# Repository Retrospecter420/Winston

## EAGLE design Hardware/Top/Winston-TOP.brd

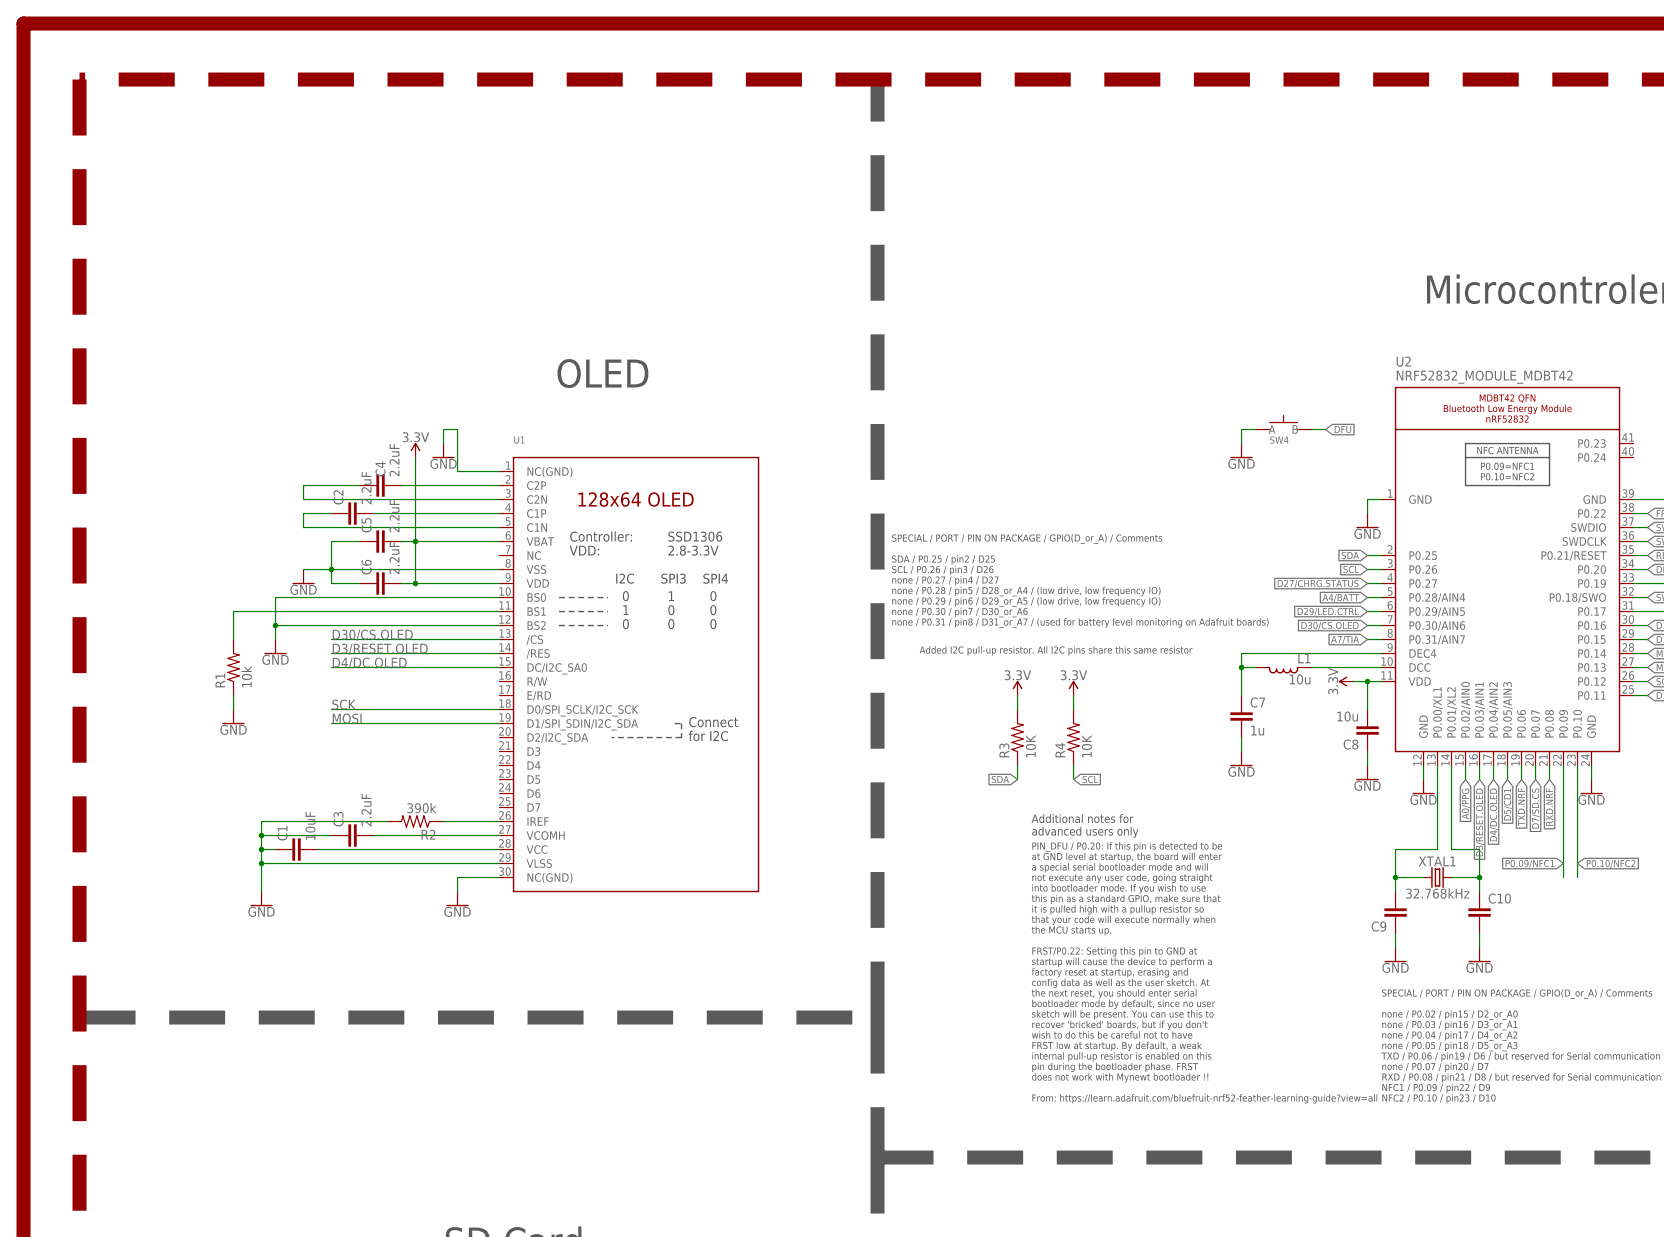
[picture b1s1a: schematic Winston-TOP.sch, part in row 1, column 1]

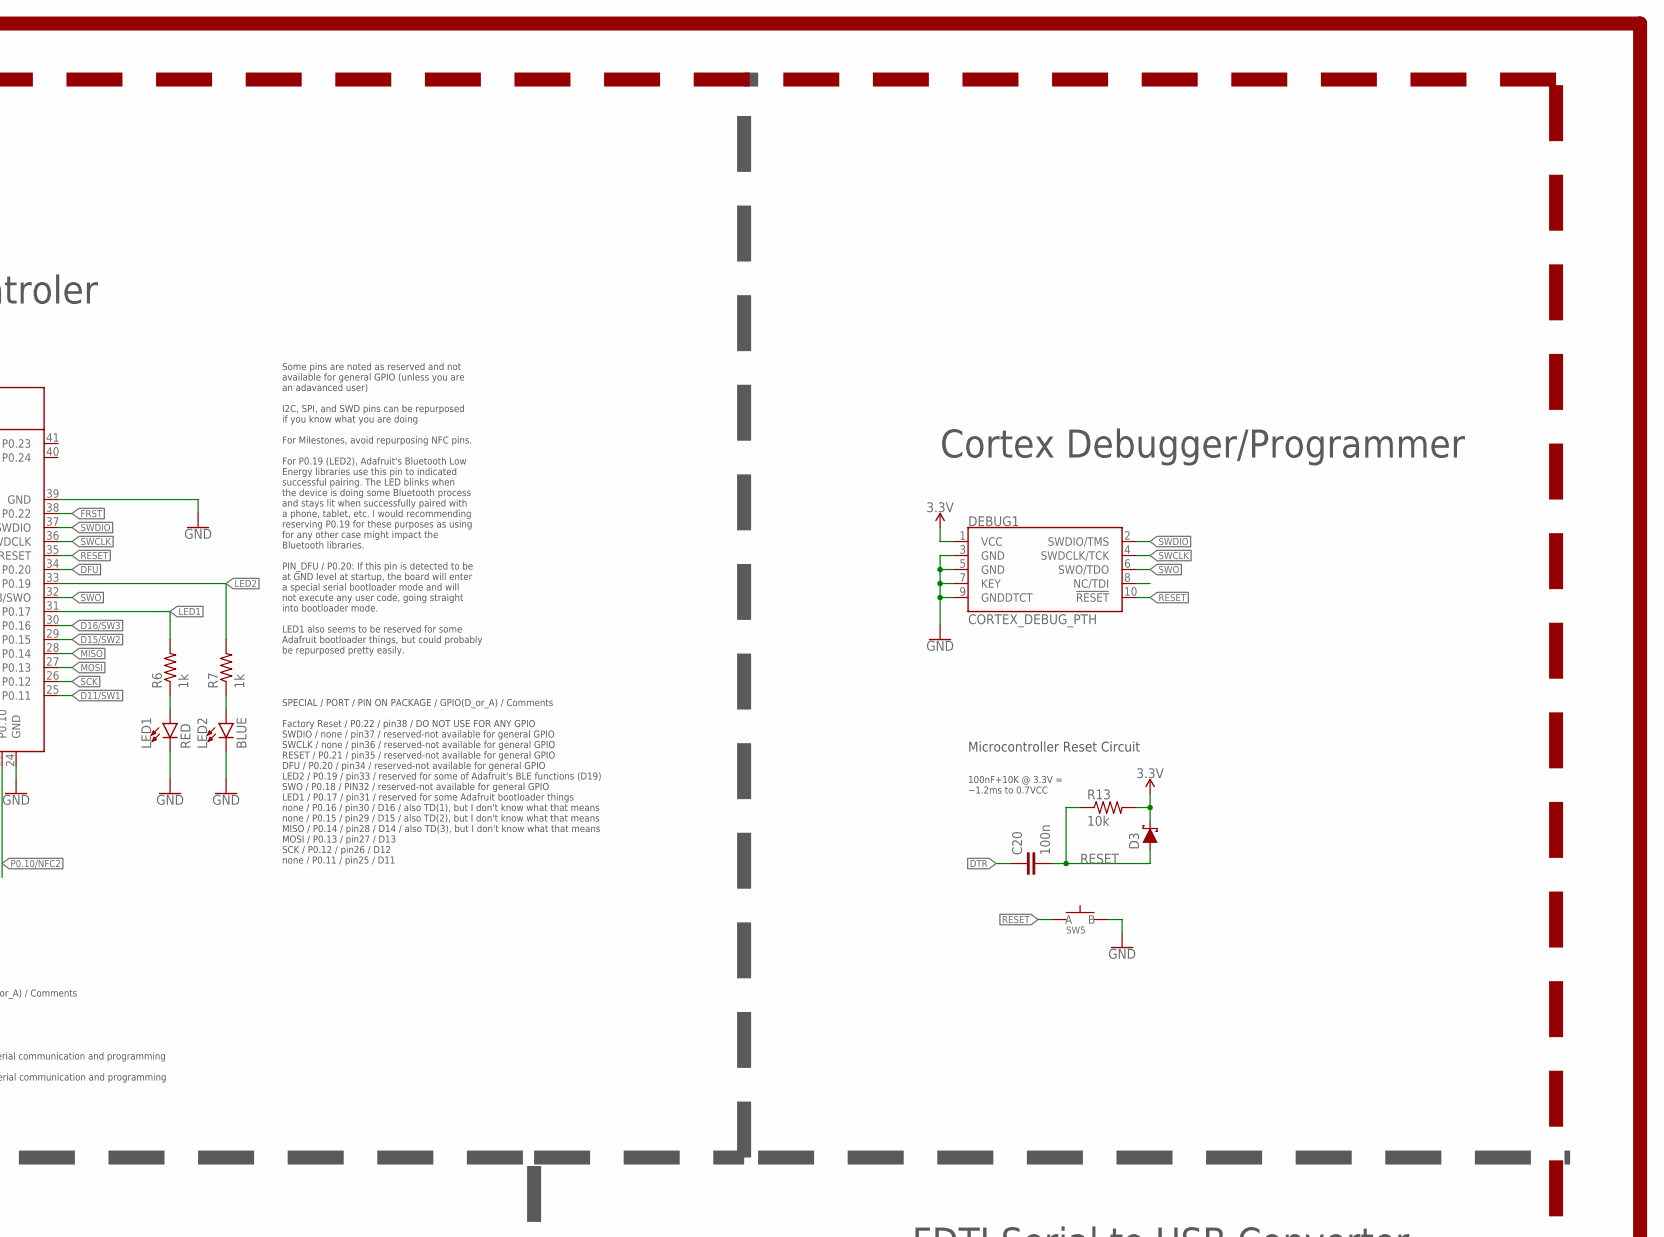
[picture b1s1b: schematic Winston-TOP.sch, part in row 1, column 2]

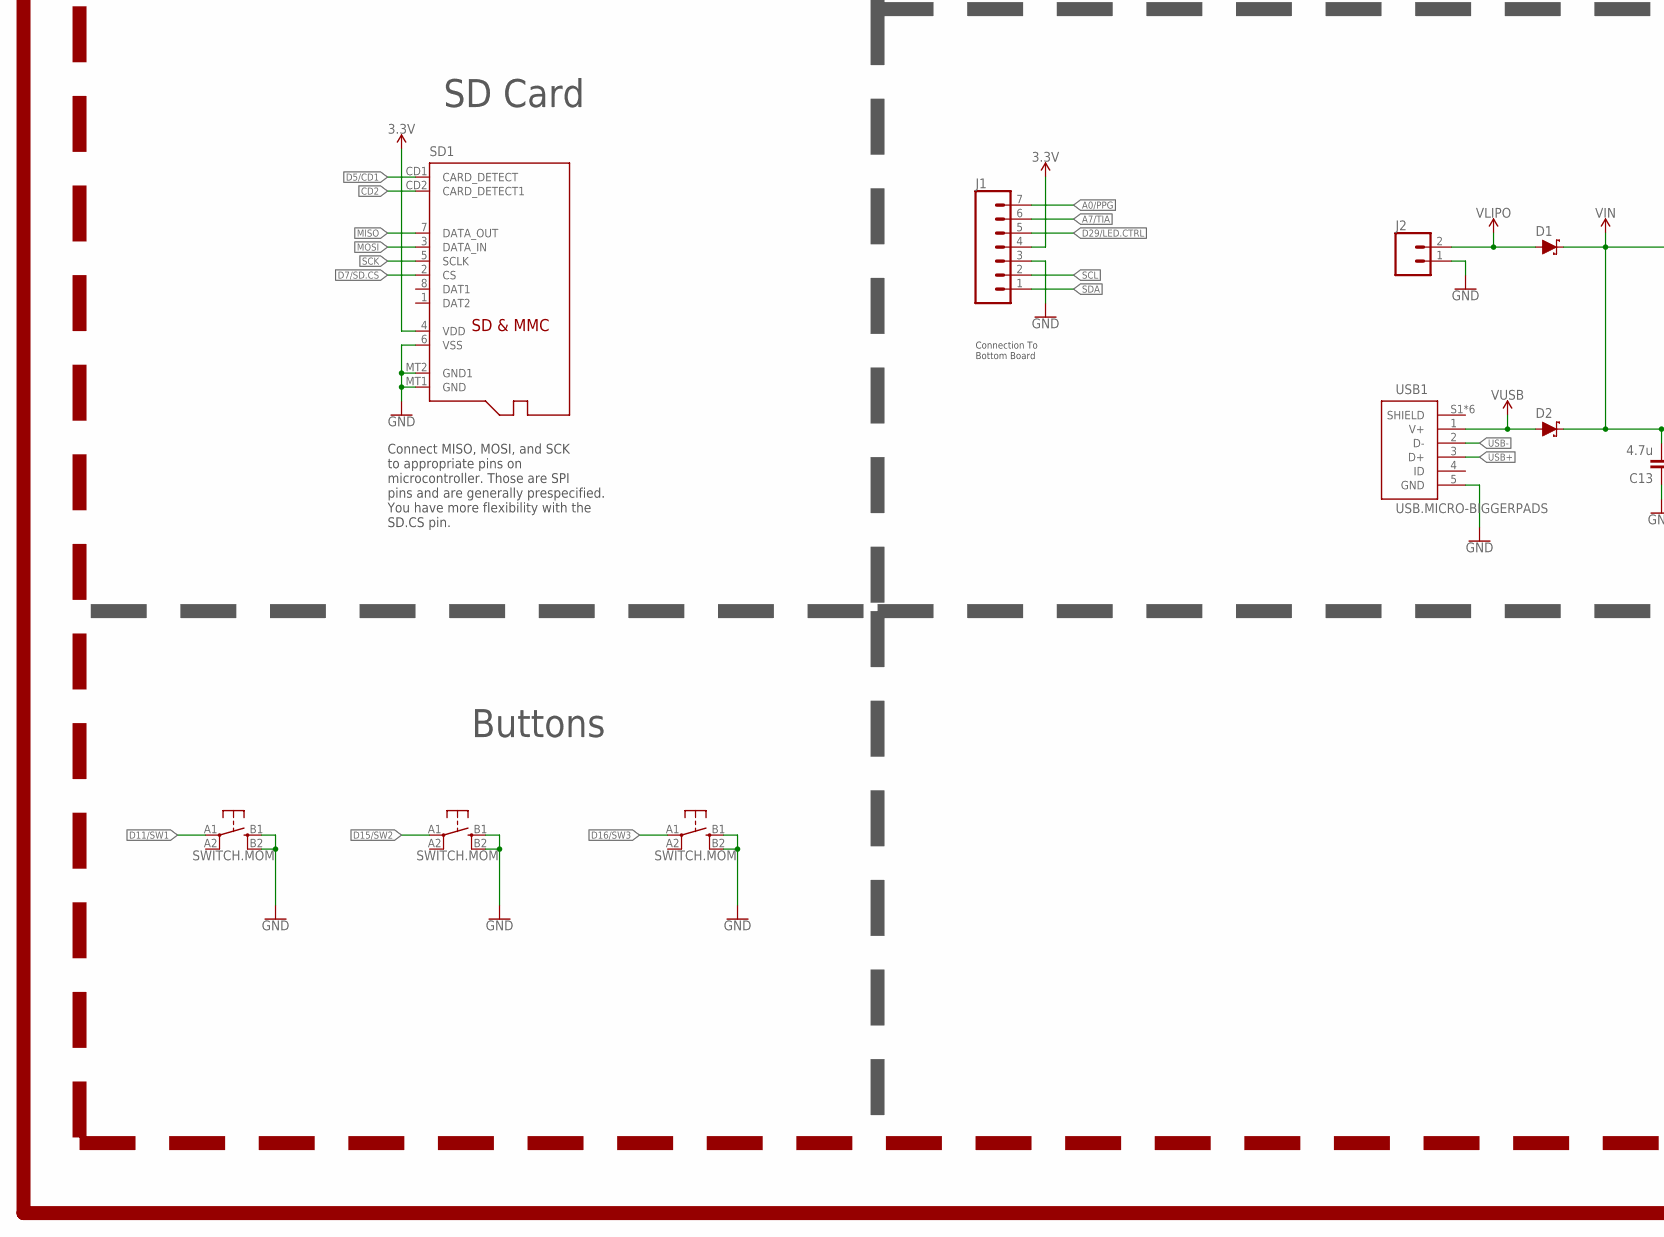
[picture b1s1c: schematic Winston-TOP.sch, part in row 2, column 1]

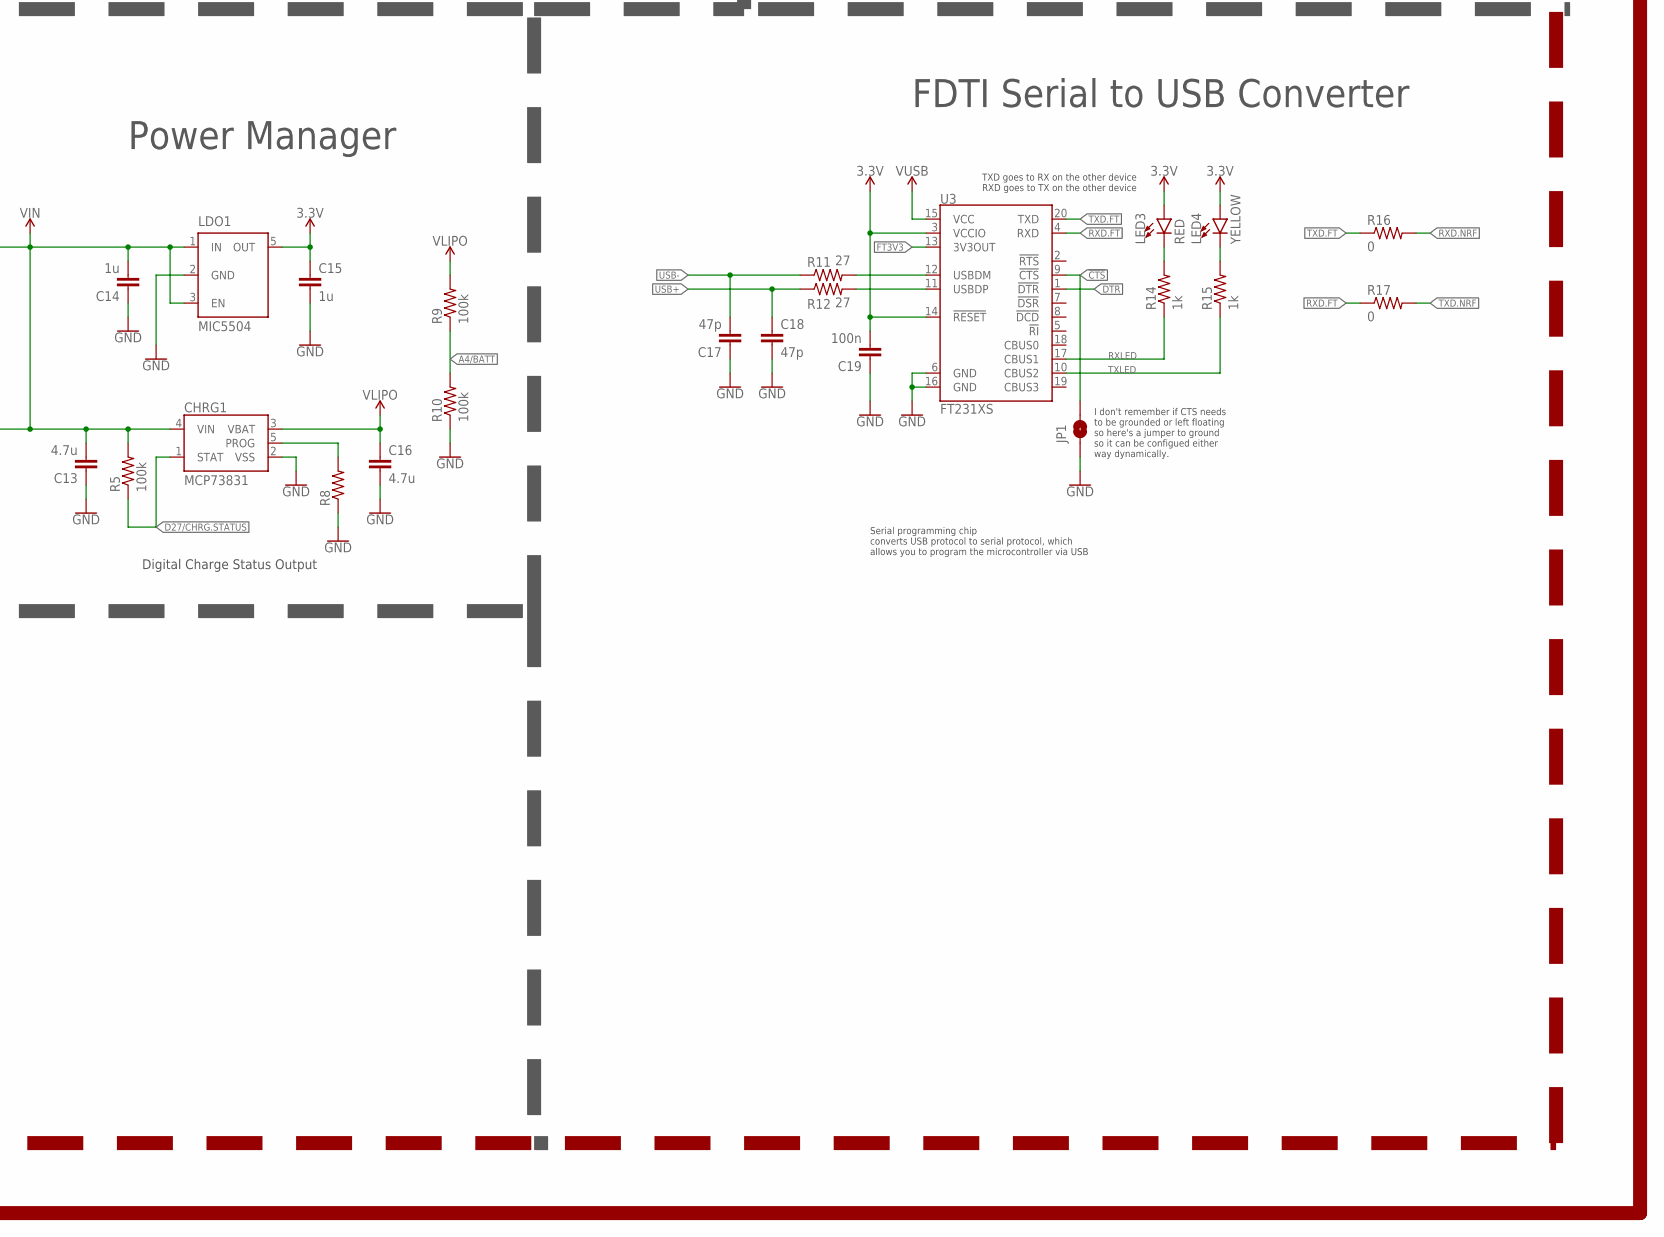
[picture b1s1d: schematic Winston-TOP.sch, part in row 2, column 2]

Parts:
C1: 10uF; C0603
C2, C3, C4, C5, C6: 2.2uF; C0402
C7, C14, C15: 1u; C0603
C8: 10u; C0805
C9, C10: CAPACITOR0603; C0603
C13, C16: 4.7u; C0603
C17, C18: 47p; C0603
C19, C20: 100n; C0603
CHRG1: MCP73831; SOT23-5
D1, D2, D3: SCHOTTKY-USC; USC
DEBUG1: CORTEX_DEBUG_PTH; 2X5-PTH-1.27MM
J1: CONN_07-1.27MM; 1X07_1.27MM
J2: CONN_02; 1X02
JP1: JUMPER-SMT_2_NO_SILK; SMT-JUMPER_2_NO_SILK
L1: 10u; L0603
LDO1: MIC5504; SOT23-5
LED1, LED3: RED; LED-0603
LED2: BLUE; LED-0603
LED4: YELLOW; LED-0603
R1, R13: 10k; R0603
R2: 390k; R0603
R3, R4: 10K; R0603
R5, R9, R10: 100k; R0603
R6, R7, R14, R15: 1k; R0603
R8: RESISTOR0603; R0603
R11, R12: 27; R0603
R16, R17: 0; R0603
SD1: MICROSD
SW1, SW2, SW3: SWITCH.MOM; TACTILE_SWITCH_SMD_6.2MM_TALL
SW4, SW5: SPST-PTS830GG140-COPY.1-3; BUTTON-GULLWING
U1: DISP_OLED_UG-2864HSWEG01-NO-WRAPAROUND; UG-2864HSWEG01_0.96IN_NO-WRAPAROUND
U2: NRF52832_MODULE_MDBT42; BLE_MODULE_RAYTAC_MDBT42
U3: FT231XS; SSOP20_L
USB1: USB.MICRO-BIGGERPADS; USB-MICRO-01.BIGGERPADS
XTAL1: 32.768kHz; 2-SMD.NOLEAD.2.0MMTO1.2MM

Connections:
3.3V: C5.2, C6.2, C8.2, C15.1, C19.2, D3.- (C), DEBUG1.1 (VCC), J1.4, LDO1.5 (OUT), LED3.A, LED4.A, R3.2, R4.2, R13.2, SD1.4 (VDD), U1.6 (VBAT), U1.9 (VDD), U2.11 (VDD), U3.3 (VCCIO), U3.14 (!RESET)
!CTS: JP1.2, U3.9 (!CTS)
A0/PPG: J1.7, U2.15 (P0.02/AIN0)
A4/BATT: R9.1, R10.2, U2.5 (P0.28/AIN4)
A7/TIA: J1.6, U2.8 (P0.31/AIN7)
CD2: SD1.CD2 (CARD_DETECT1)
D3/RESET.OLED: U1.14 (/RES), U2.16 (P0.03/AIN1)
D4/DC.OLED: U1.15 (DC/I2C_SA0), U2.17 (P0.04/AIN2)
D5/CD1: SD1.CD1 (CARD_DETECT), U2.18 (P0.05/AIN3)
D7/SD.CS: SD1.2 (CS), U2.20 (P0.07)
D11/SW1: SW1.A1 (1), U2.25 (P0.11)
D15/SW2: SW2.A1 (1), U2.29 (P0.15)
D16/SW3: SW3.A1 (1), U2.30 (P0.16)
D27/CHRG.STATUS: CHRG1.1 (STAT), R5.1, U2.4 (P0.27)
D29/LED.CTRL: J1.5, U2.6 (P0.29/AIN5)
D30/CS.OLED: U1.13 (/CS), U2.7 (P0.30/AIN6)
DFU: SW4.3 (B), U2.34 (P0.20)
DTR: C20.1, U3.1 (!DTR)
FRST: U2.38 (P0.22)
FT3V3: U3.13 (3V3OUT)
GND: C1.1, C3.1, C5.1, C6.1, C7.2, C8.1, C9.1, C10.2, C13.1, C14.1, C15.2, C16.2, C17.1, C18.2, C19.1, CHRG1.2 (VSS), DEBUG1.3 (GND), DEBUG1.5 (GND), DEBUG1.7 (KEY), DEBUG1.9 (GNDDTCT), J1.3, J2.1, JP1.1, LDO1.2 (GND), LED1.C, LED2.C, R1.1, R2.2, R8.1, R10.1, SD1.6 (VSS), SD1.MT1 (GND), SD1.MT2 (GND1), SW1.B1 (3), SW1.B2 (4), SW2.B1 (3), SW2.B2 (4), SW3.B1 (3), SW3.B2 (4), SW4.1 (A), SW5.3 (B), U1.1 (NC(GND)), U1.8 (VSS), U1.10 (BS0), U1.12 (BS2), U1.29 (VLSS), U1.30 (NC(GND)), U2.1 (GND), U2.12 (GND), U2.24 (GND), U2.39 (GND), U3.6 (GND), U3.16 (GND), USB1.5 (GND)
LED1: R6.2, U2.31 (P0.17)
LED2: R7.2, U2.33 (P0.19)
MISO: SD1.7 (DATA_OUT), U2.28 (P0.14)
MOSI: SD1.3 (DATA_IN), U1.19 (D1/SPI_SDIN/I2C_SDA), U2.27 (P0.13)
unnamed: R1.2, U1.11 (BS1)
unnamed: R2.1, U1.26 (IREF)
unnamed: C4.2, U1.2 (C2P)
unnamed: C9.2, U2.13 (P0.00/XL1), XTAL1.P$1 (1)
unnamed: C4.1, U1.3 (C2N)
unnamed: C10.1, U2.14 (P0.01/XL2), XTAL1.P$2 (2)
unnamed: C2.2, U1.4 (C1P)
unnamed: C2.1, U1.5 (C1N)
unnamed: LED1.A, R6.1
unnamed: LED2.A, R7.1
unnamed: L1.1, U2.10 (DCC)
unnamed: C7.1, L1.2, U2.9 (DEC4)
unnamed: C1.2, U1.28 (VCC)
unnamed: C3.2, U1.27 (VCOMH)
unnamed: CHRG1.5 (PROG), R8.2
unnamed: R11.2, U3.12 (USBDM)
unnamed: R12.2, U3.11 (USBDP)
unnamed: LED3.C, R14.2
unnamed: LED4.C, R15.2
P0.09/NFC1: U2.22 (P0.09)
P0.10/NFC2: U2.23 (P0.10)
RESET: C20.2, D3.+ (A), DEBUG1.10 (!RESET), R13.1, SW5.1 (A), U2.35 (P0.21/RESET)
RXD.FT: R17.1, U3.4 (RXD)
RXD.NRF: R16.2, U2.21 (P0.08)
RXLED: R14.1, U3.17 (CBUS1)
SCK: SD1.5 (SCLK), U1.18 (D0/SPI_SCLK/I2C_SCK), U2.26 (P0.12)
SCL: J1.2, R4.1, U2.3 (P0.26)
SDA: J1.1, R3.1, U2.2 (P0.25)
SWCLK: DEBUG1.4 (SWDCLK/TCK), U2.36 (SWDCLK)
SWDIO: DEBUG1.2 (SWDIO/TMS), U2.37 (SWDIO)
SWO: DEBUG1.6 (SWO/TDO), U2.32 (P0.18/SWO)
TXD.FT: R16.1, U3.20 (TXD)
TXD.NRF: R17.2, U2.19 (P0.06)
TXLED: R15.1, U3.10 (CBUS2)
USB+: C18.1, R12.1, USB1.3 (D+)
USB-: C17.2, R11.1, USB1.2 (D-)
VIN: C13.2, C14.2, CHRG1.4 (VIN), D1.- (C), D2.- (C), LDO1.1 (IN), LDO1.3 (EN), R5.2
VLIPO: C16.1, CHRG1.3 (VBAT), D1.+ (A), J2.2, R9.2
V_USB: D2.+ (A), U3.15 (VCC), USB1.1 (V+)

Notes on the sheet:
Microcontroller Reset Circuit
100nF+10K @ 3.3V = ~1.2ms to 0.7VCC
SPECIAL / PORT / PIN ON PACKAGE / GPIO(D_or_A) / Comments SDA / P0.25 / pin2 / D25 SCL / P0.26 / pin3 / D26 none / P0.27 / pin4 / D27 none / P0.28 / pin5 / D28_or_A4 / (low drive, low frequency IO) none / P0.29 / pin6 / D29_or_A5 / (low drive, low frequency IO) none / P0.30 / pin7 / D30_or_A6 none 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
SPECIAL / PORT / PIN ON PACKAGE / GPIO(D_or_A) / Comments none / P0.02 / pin15 / D2_or_A0 none / P0.03 / pin16 / D3_or_A1 none / P0.04 / pin17 / D4_or_A2 none / P0.05 / pin18 / D5_or_A3 TXD / P0.06 / pin19 / D6 / but reserved for Serial communication and programming none / P0.07 / pin20 / D7 RXD / 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
SPECIAL / PORT / PIN ON PACKAGE / GPIO(D_or_A) / Comments Factory Reset / P0.22 / pin38 / DO NOT USE FOR ANY GPIO SWDIO / none / pin37 / reserved-not available for general GPIO SWCLK / none / pin36 / reserved-not available for general GPIO RESET / P0.21 / pin35 / reserved-not available for general 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
Some pins are noted as reserved and not available for general GPIO (unless you are an adavanced user) I2C, SPI, and SWD pins can be repurposed if you know what you are doing For Milestones, avoid repurposing NFC pins. For P0.19 (LED2), Adafruit's Bluetooth Low Energy libraries use this pin to indic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
PIN_DFU / P0.20: If this pin is detected to be at GND level at startup, the board will enter a special serial bootloader mode and will not execute any user code, going straight into bootloader mode. If you wish to use this pin as a standard GPIO, make sure that it is pulled high with a pullup resis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
Additional notes for advanced users only
Connect MISO, MOSI, and SCK to appropriate pins on microcontroller. Those are SPI pins and are generally prespecified. You have more flexibility with the SD.CS pin.
Microcontroler
OLED
Power Manager
SD Card
Buttons
Cortex Debugger/Programmer
TXD goes to RX on the other device RXD goes to TX on the other device
I don't remember if CTS needs to be grounded or left floating so here's a jumper to ground so it can be configued either way dynamically.
FDTI Serial to USB Converter
Added I2C pull-up resistor. All I2C pins share this same resistor
Serial programming chip converts USB protocol to serial protocol, which allows you to program the microcontroller via USB
Connection To Bottom Board
Digital Charge Status Output

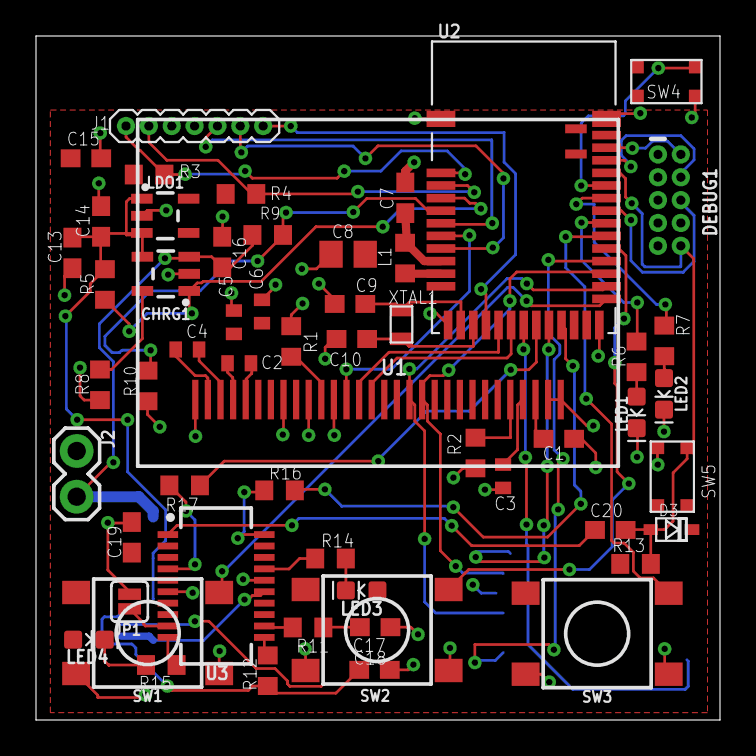
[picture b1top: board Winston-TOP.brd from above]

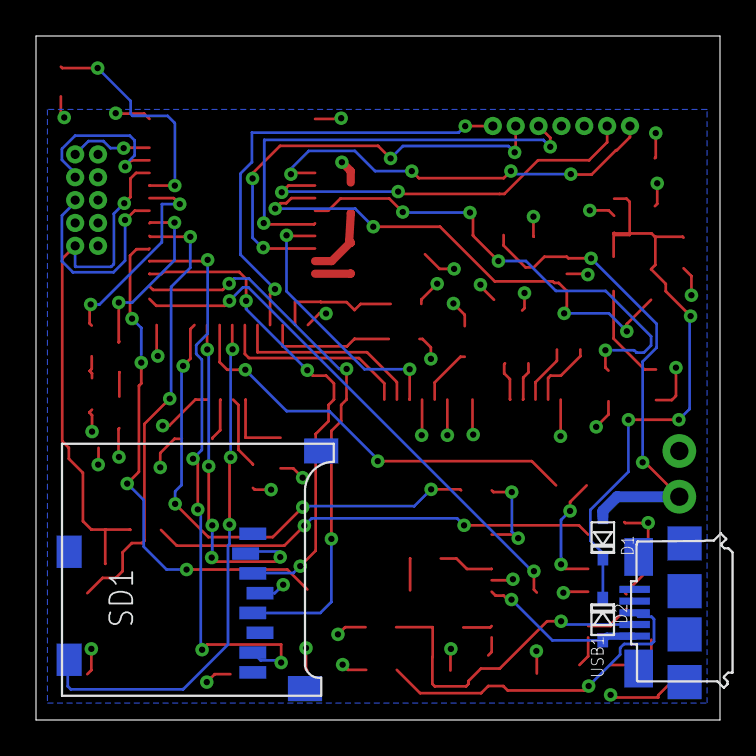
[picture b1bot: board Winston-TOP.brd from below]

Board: 2 copper layers, 38.0 x 38.0 mm, 60 parts (4 on the bottom side), 59 nets.

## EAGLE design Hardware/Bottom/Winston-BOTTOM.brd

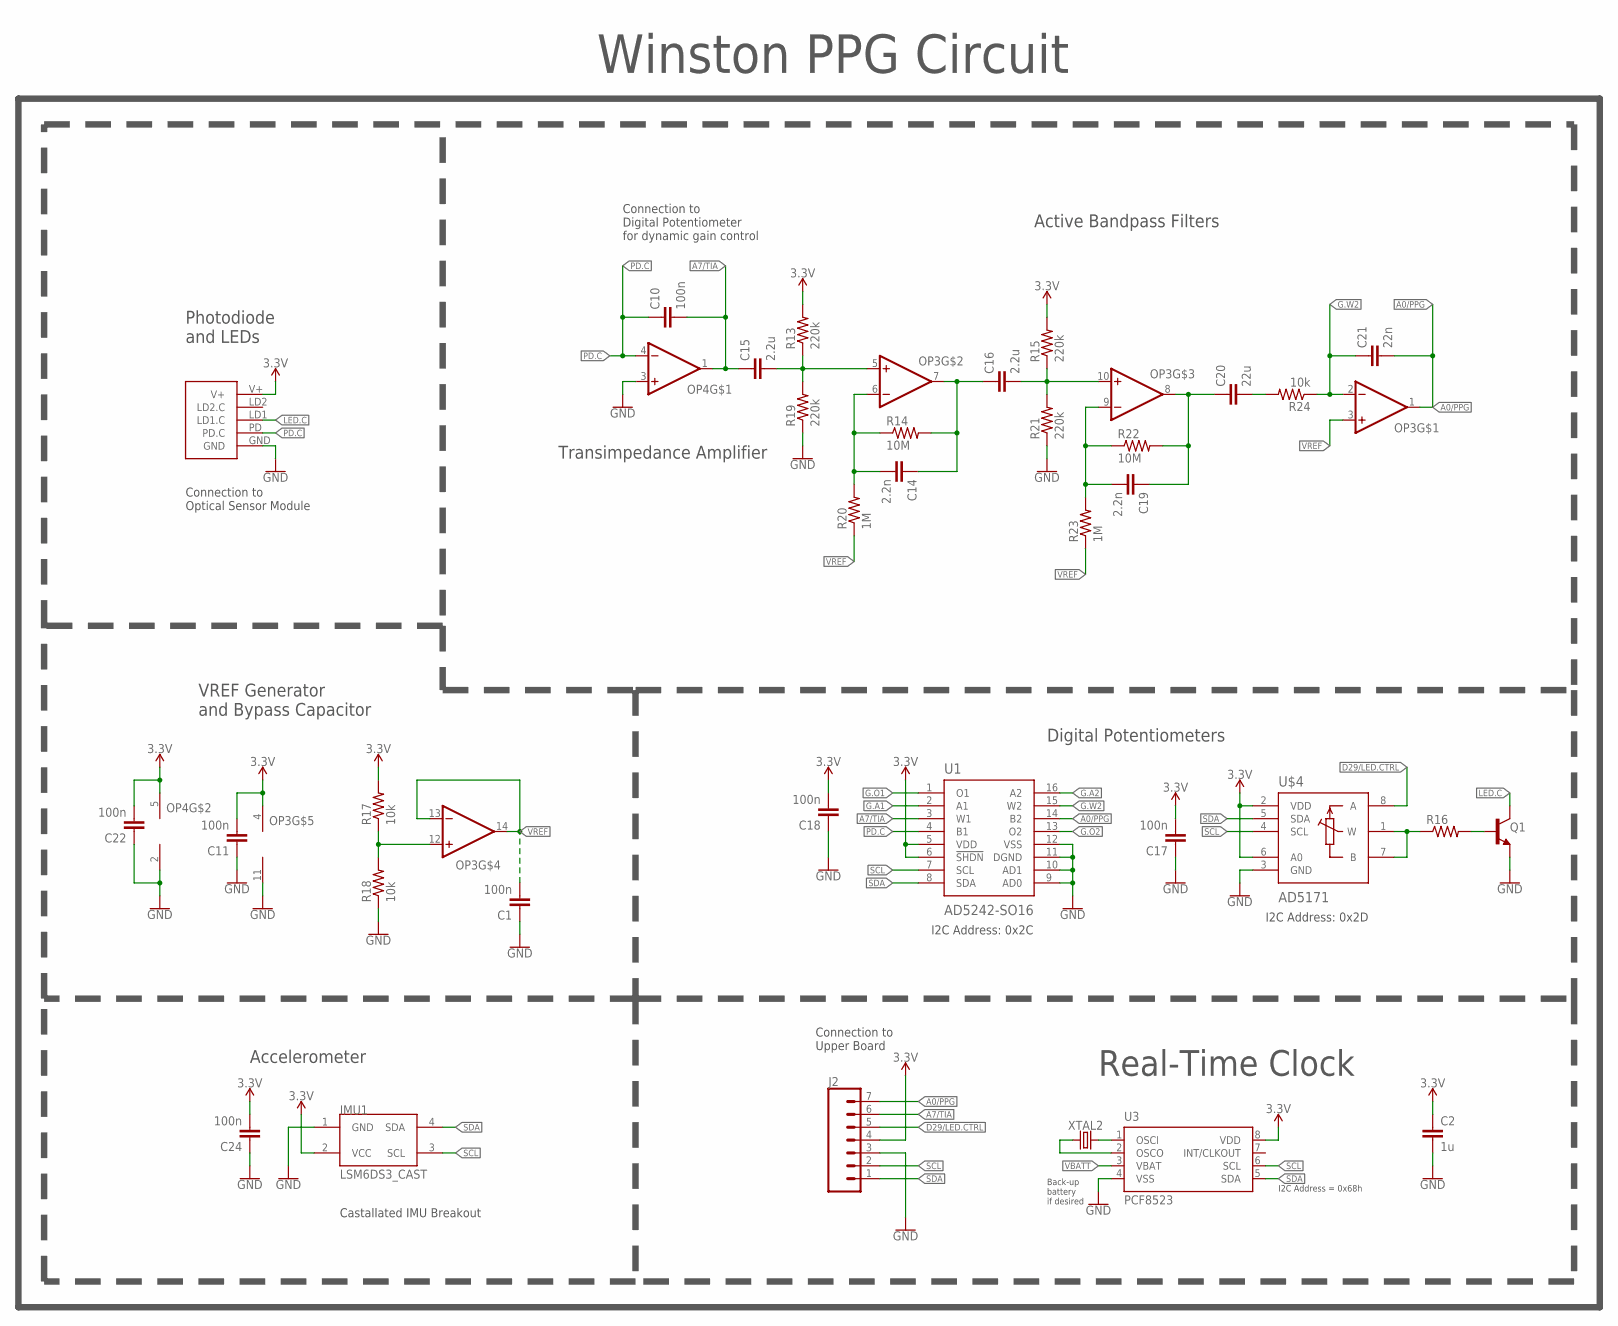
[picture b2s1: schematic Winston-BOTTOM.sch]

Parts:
C1, C10, C11, C17, C18, C22, C24: 100n; C0603
C2: 1u; C0603
C14, C19: 2.2n; C0603
C15, C16: 2.2u; C0603
C20: 22u; C0603
C21: 22n; C0603
IMU1: LSM6DS3_CAST
J2: CONN_07-1.27MM; 1X07_1.27MM
OP3: OP-QUAD-SO14; SO14
OP4: OP-SINGLEOT; SOT23-5
Q1: NPN-GENERIC; SOT23-3
R13, R15, R19, R21: 220k; R0603
R14, R22: 10M; R0603
R16: RESISTOR0603; R0603
R17, R18: 10k; R0402
R20, R23: 1M; R0603
R24: 10k; R0603
U1: AD5242-SO16; SO16
U3: PCF8523; SO8; DIGIKEY 568-5306-1-ND
U$3: PPG.MODULE.2
U$4: AD5171; SOT-23-8
XTAL2: 32.7680kHz; 2-SMD.NOLEAD.2.0MMTO1.2MM

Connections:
3.3V: C2.1, C11.2, C17.2, C18.2, C22.2, C24.2, IMU1.2 (VCC), J2.4, OP3.4 (V+), OP4.5 (V+), R13.2, R15.2, R17.2, U1.5 (VDD), U1.6 (!SHDN), U3.8 (VDD), U$3.V+, U$4.2 (VDD), U$4.6 (A0)
A0/PPG: C21.2, J2.7, OP3.1 (OUT), U1.14 (B2)
A7/TIA: C10.2, C15.1, J2.6, OP4.1 (OUT), U1.3 (W1)
D29/LED.CTRL: J2.5, U$4.8 (A)
G.A1: U1.2 (A1)
G.A2: U1.16 (A2)
G.O1: U1.1 (O1)
G.O2: U1.13 (O2)
G.W2: C21.1, OP3.2 (-IN), R24.1, U1.15 (W2)
GND: C1.1, C2.2, C11.1, C17.1, C18.1, C22.1, C24.1, IMU1.1 (GND), J2.3, OP3.11 (V-), OP4.2 (V-), OP4.3 (+IN), Q1.2 (E), R18.1, R19.1, R21.1, U1.9 (AD0), U1.10 (AD1), U1.11 (DGND), U1.12 (VSS), U3.4 (VSS), U$3.GND, U$4.3 (GND)
LED.C: Q1.3 (C), U$3.LD1 (LD1.C)
unnamed: U3.2 (OSCO), XTAL2.P$1 (1)
unnamed: U3.1 (OSCI), XTAL2.P$2 (2)
unnamed: Q1.1 (B), R16.2
unnamed: R16.1, U$4.1 (W), U$4.7 (B)
unnamed: OP3.12 (+IN), R17.1, R18.2
unnamed: C15.2, OP3.5 (+IN), R13.1, R19.2
unnamed: C14.2, OP3.6 (-IN), R14.1, R20.2
unnamed: C14.1, C16.1, OP3.7 (OUT), R14.2
unnamed: C16.2, OP3.10 (+IN), R15.1, R21.2
unnamed: C19.2, OP3.9 (-IN), R22.1, R23.2
unnamed: C19.1, C20.1, OP3.8 (OUT), R22.2
unnamed: C20.2, R24.2
PD.C: C10.1, OP4.4 (-IN), U1.4 (B1), U$3.PD (PD.C)
SCL: IMU1.3 (SCL), J2.2, U1.7 (SCL), U3.6 (SCL), U$4.4 (SCL)
SDA: IMU1.4 (SDA), J2.1, U1.8 (SDA), U3.5 (SDA), U$4.5 (SDA)
VBATT: U3.3 (VBAT)
VREF: C1.2, OP3.3 (+IN), OP3.13 (-IN), OP3.14 (OUT), R20.1, R23.1

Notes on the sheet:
Photodiode and LEDs
Active Bandpass Filters
Digital Potentiometers
Transimpedance Amplifier
I2C Address: 0x2C
I2C Address: 0x2D
Accelerometer
Connection to Optical Sensor Module
Connection to Digital Potentiometer for dynamic gain control
Connection to Upper Board
Castallated IMU Breakout
VREF Generator and Bypass Capacitor
Winston PPG Circuit
I2C Address = 0x68h
Back-up battery if desired
Real-Time Clock

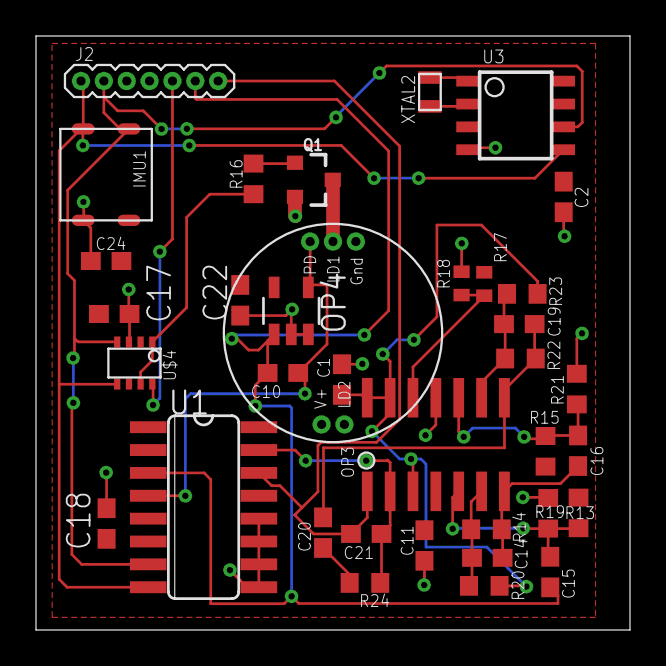
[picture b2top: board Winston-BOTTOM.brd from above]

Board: 2 copper layers, 33.0 x 33.0 mm, 36 parts (0 on the bottom side), 23 nets.

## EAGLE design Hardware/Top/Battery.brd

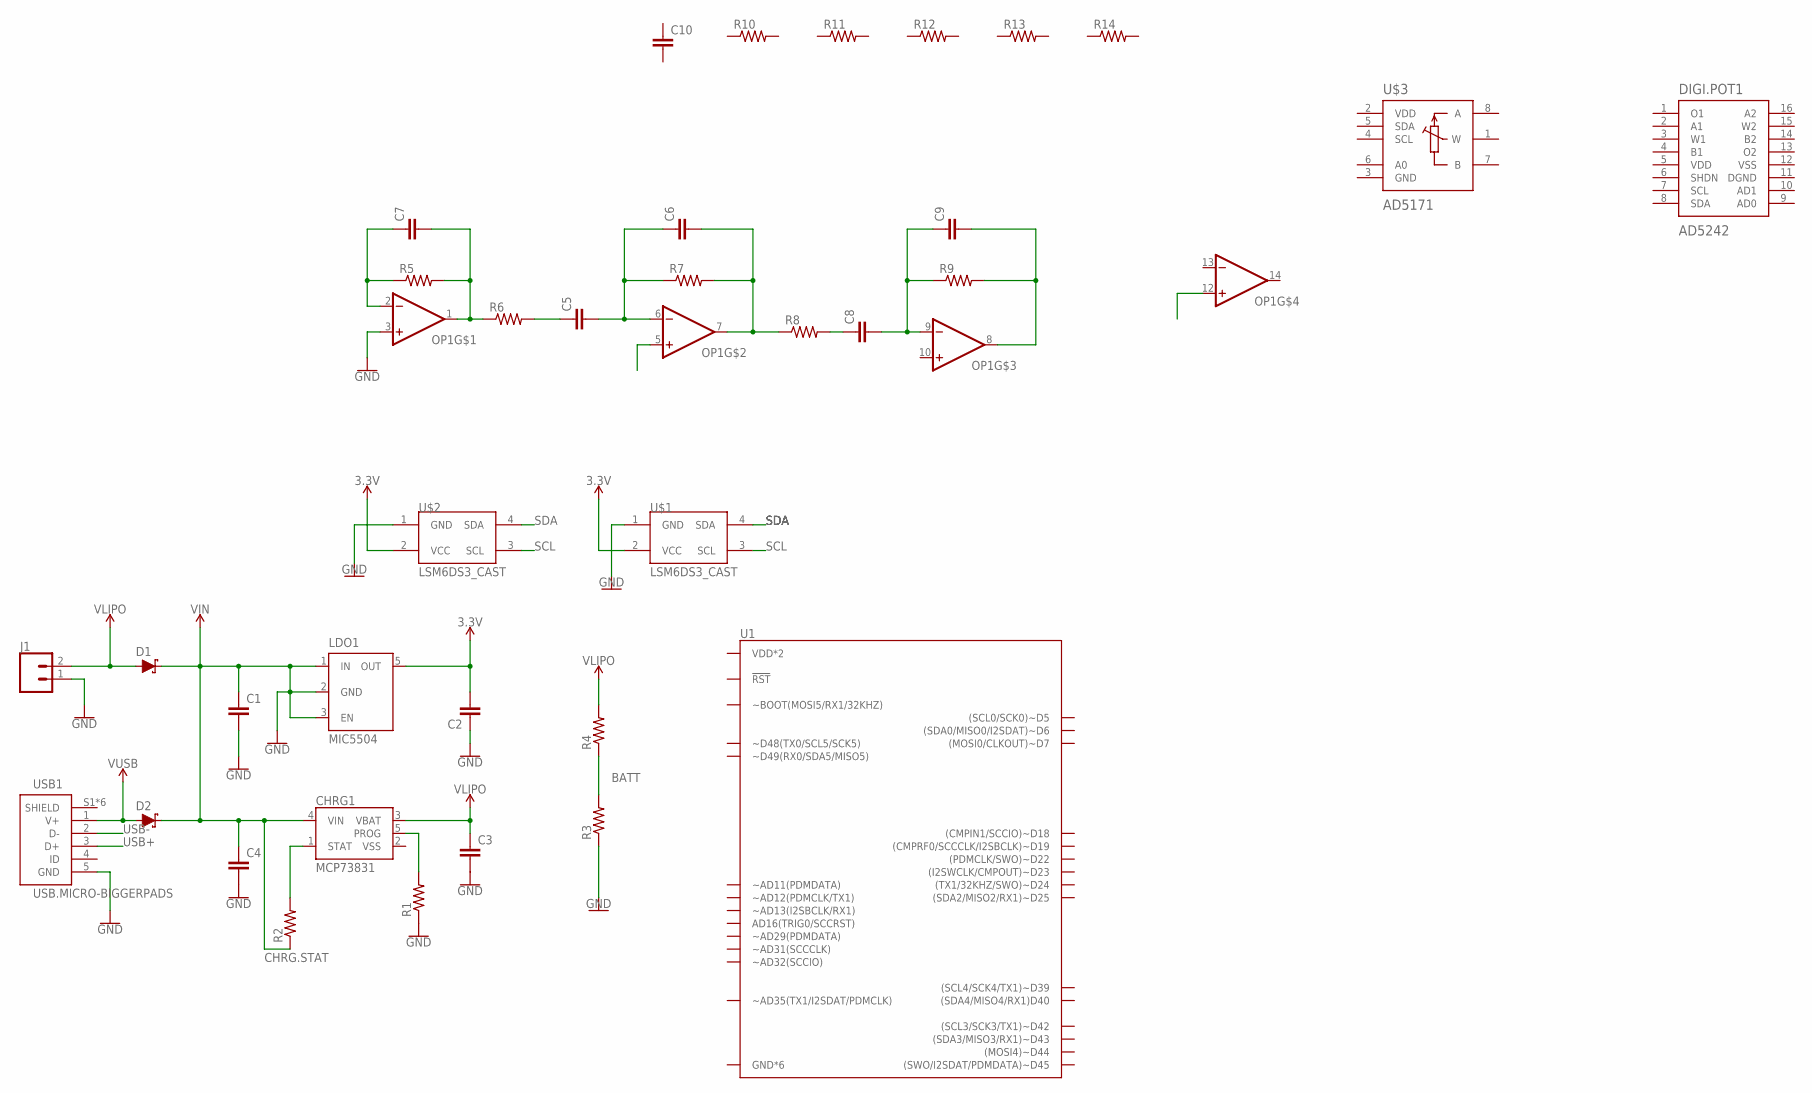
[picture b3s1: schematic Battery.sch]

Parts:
C1, C2, C3, C4, C5, C6, C7, C8, C9, C10: CAPACITOR0603; C0603
CHRG1: MCP73831; SOT23-5
D1, D2: SCHOTTKY-USC; USC
DIGI.POT1: AD5242; TSSOP16
J1: CONN_02; 1X02
LDO1: MIC5504; SOT23-5
OP1: OP-QUAD-SO14; SO14
R1, R2, R3, R4, R5, R6, R7, R8, R9, R10, R11, R12, R13, R14: RESISTOR0603; R0603
U1: ARTEMIS.CAST; ARTEMIS_CAST
U$1, U$2: LSM6DS3_CAST
U$3: AD5171; SOT-23-8
USB1: USB.MICRO-BIGGERPADS; USB-MICRO-01.BIGGERPADS

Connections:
3.3V: C2.2, LDO1.5 (OUT), U$1.2 (VCC), U$2.2 (VCC)
BATT: R3.2, R4.1
CHRG.STAT: C1.1, C4.1, CHRG1.4 (VIN), D1.- (C), D2.- (C), LDO1.1 (IN), LDO1.2 (GND), LDO1.3 (EN), R2.1
GND: C1.2, C2.1, C3.2, C4.2, J1.1, OP1.3 (+IN), R1.1, R3.1, U$1.1 (GND), U$2.1 (GND), USB1.5 (GND)
unnamed: C7.1, OP1.2 (-IN), R5.1
unnamed: C7.2, OP1.1 (OUT), R5.2, R6.1
unnamed: C5.1, R6.2
unnamed: C5.2, C6.1, OP1.6 (-IN), R7.1
unnamed: CHRG1.1 (STAT), R2.2
unnamed: CHRG1.5 (PROG), R1.2
unnamed: C6.2, OP1.7 (OUT), R7.2, R8.1
unnamed: C8.1, R8.2
unnamed: C8.2, C9.1, OP1.9 (-IN), R9.1
unnamed: C9.2, OP1.8 (OUT), R9.2
SCL: U$1.3 (SCL), U$2.3 (SCL)
SDA: U$1.4 (SDA), U$2.4 (SDA)
USB+: USB1.3 (D+)
USB-: USB1.2 (D-)
V+: OP1.4 (V+)
V-: OP1.11 (V-)
VLIPO: C3.1, CHRG1.3 (VBAT), D1.+ (A), J1.2, R4.2
VSS: CHRG1.2 (VSS)
V_USB: D2.+ (A), USB1.1 (V+)

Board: 2 copper layers, 36 parts (0 on the bottom side), 18 nets, no tracks yet.

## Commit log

2020-02-02 software and hardware for smartwatch
2020-06-04 Smartwatch Capabilities document
2020-06-04 updated Hardware folder with schematics
2020-06-04 updateded BOM
2020-06-04 updated Hardware files
2020-06-04 updated Hardware File
2020-06-04 updated main directory
2020-06-04 updated directory
2020-06-04 removed the autosaves
2020-06-05 added .gitignore into main directory
2020-06-05 removed extra smartwatch capabilities doc
2020-06-05 updated to fix typo
2020-06-11 updated top and bottom boards with everything from Take 002
2020-07-02 routed the top board
2020-07-02 finished routing all boards
2020-07-17 continued routing top board
2020-07-30 Completed Routing Top Board
